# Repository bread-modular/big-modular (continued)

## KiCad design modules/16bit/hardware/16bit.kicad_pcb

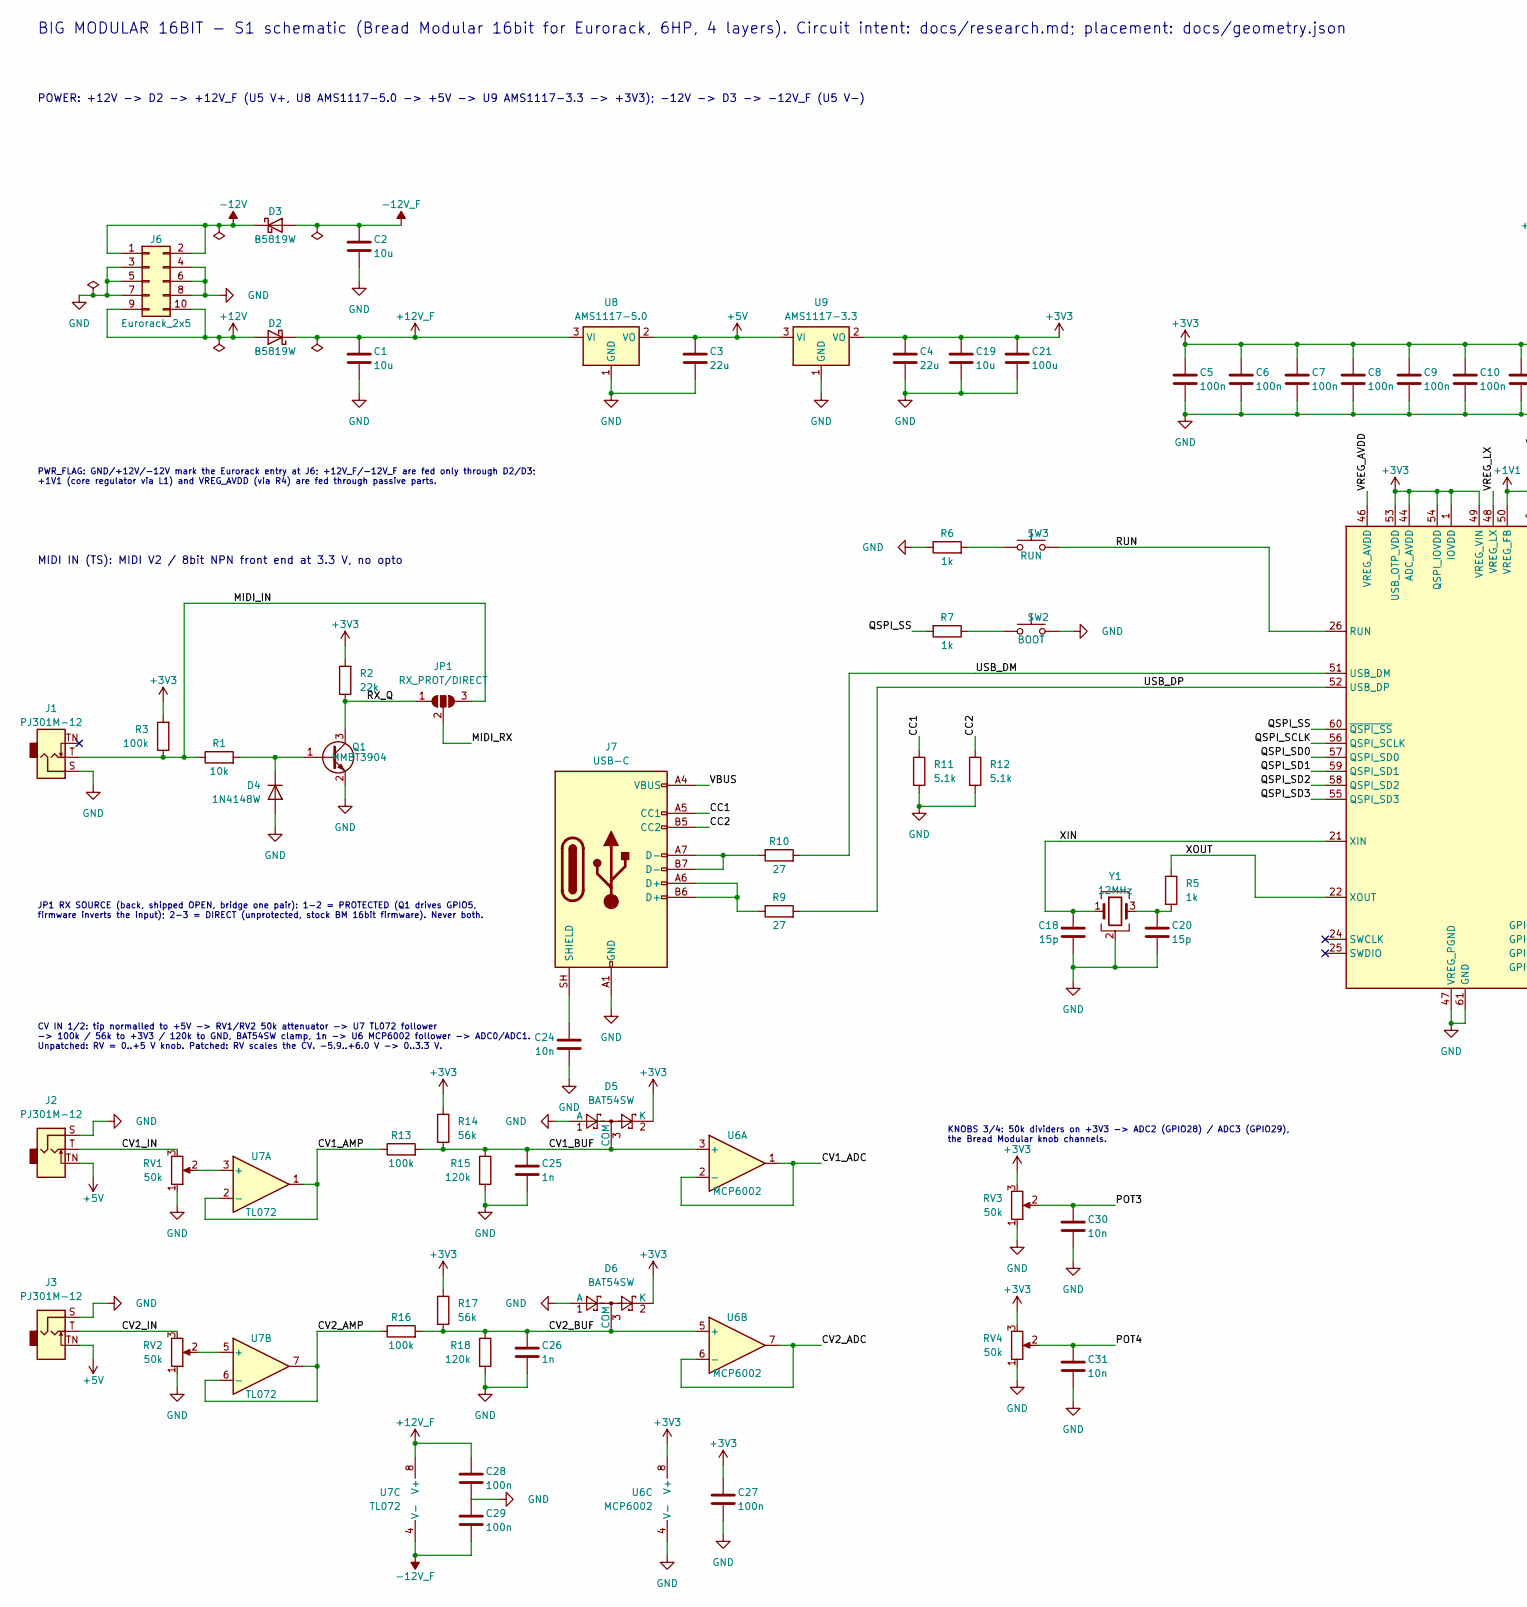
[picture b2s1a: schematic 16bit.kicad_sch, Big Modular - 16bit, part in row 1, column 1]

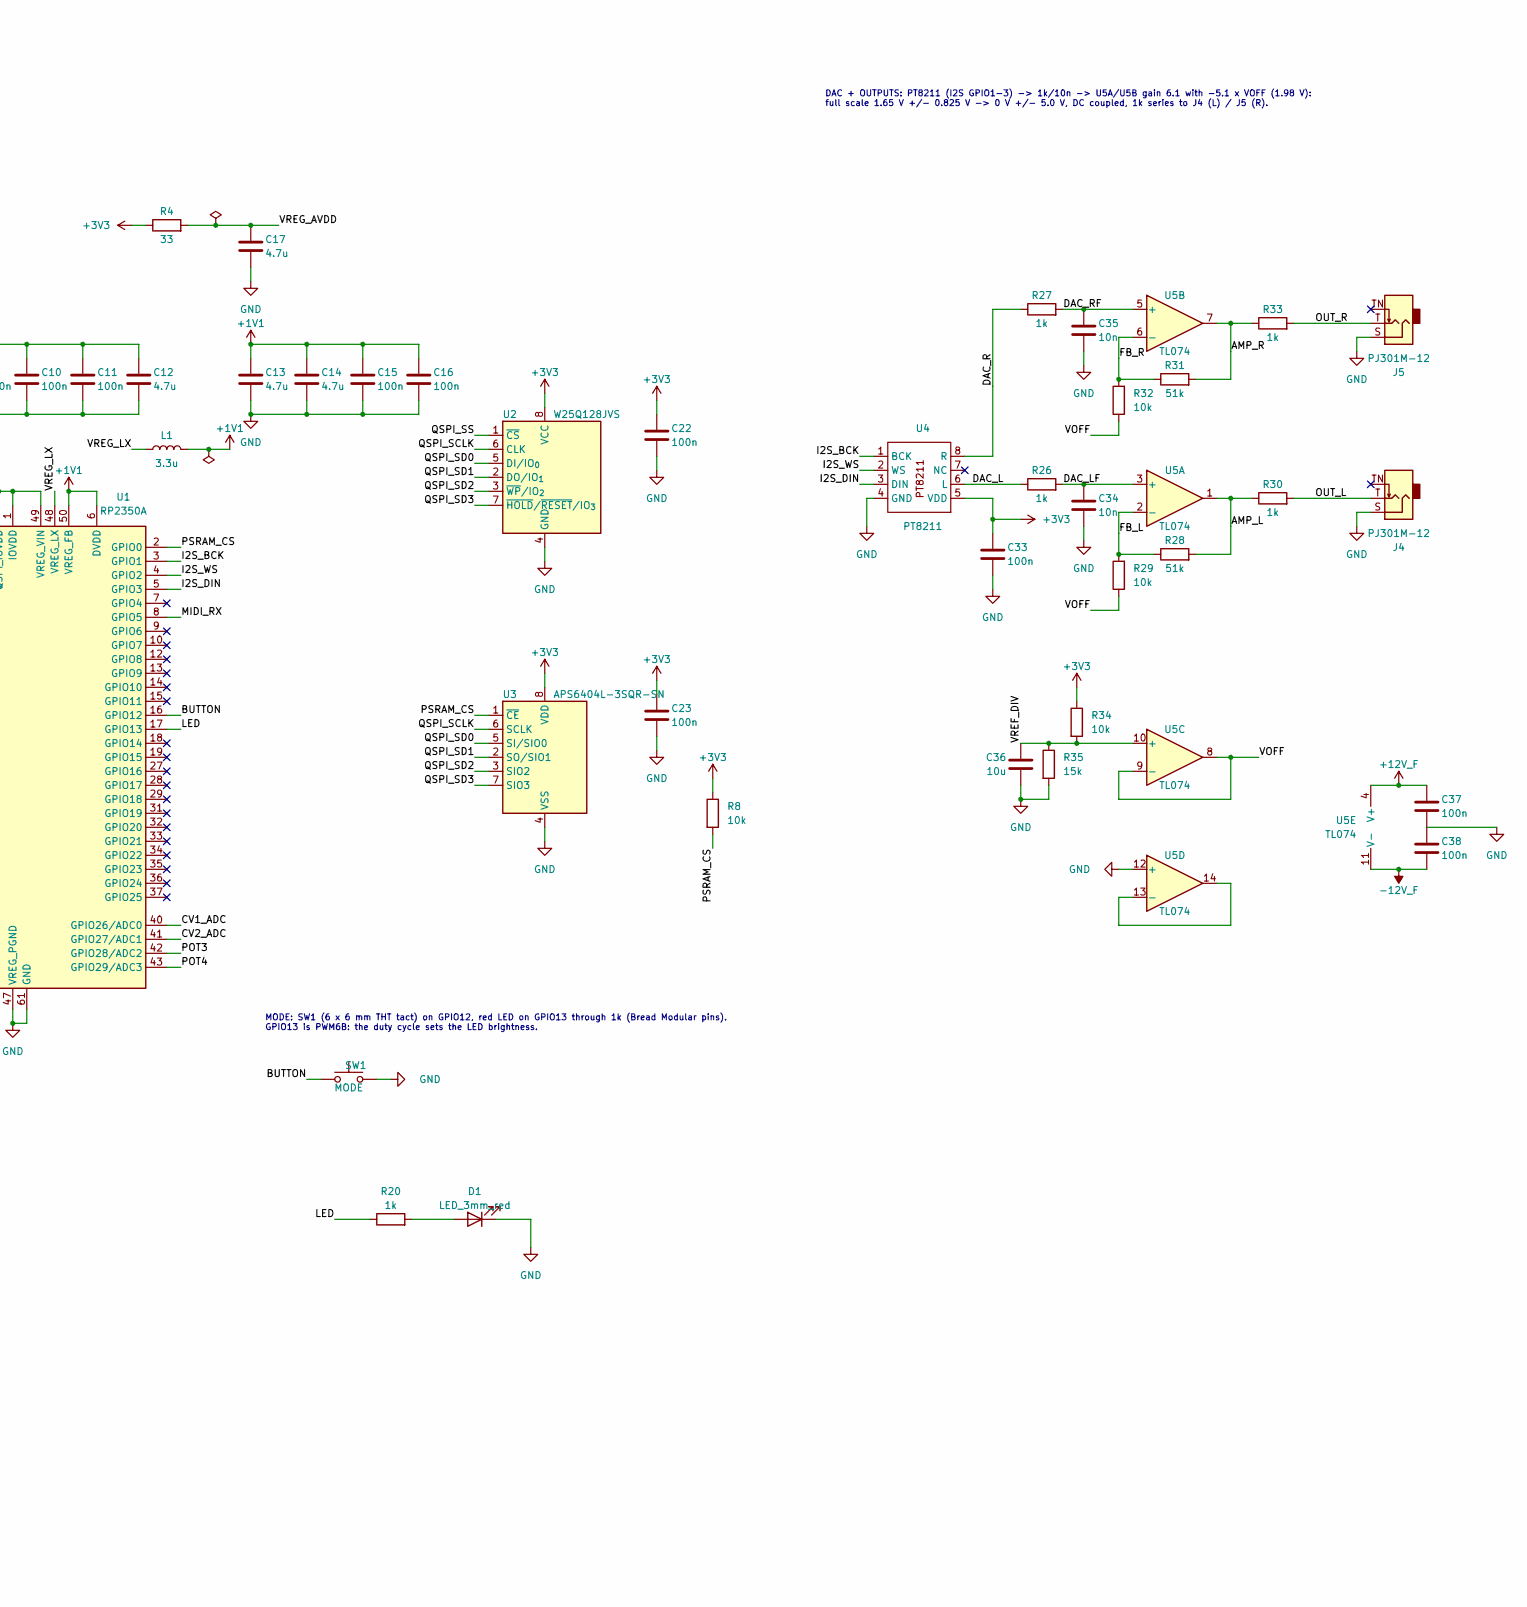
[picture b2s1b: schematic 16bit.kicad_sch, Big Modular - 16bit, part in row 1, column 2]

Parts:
C1, C2, C19, C36: 10u; C_0805_2012Metric; Voltage 25V; MPN CL21A106KAYNNNE; LCSC C15850
C3, C4: 22u; C_0805_2012Metric; Voltage 25V; MPN CL21A226MAQNNNE; LCSC C45783
C5, C6, C7, C8, C9, C10, C11, C22, C23, C33: 100n; C_0402_1005Metric; Voltage 16V; MPN CL05B104KO5NNNC; LCSC C1525
C12, C13: 4.7u; C_0402_1005Metric_small_pads; Voltage 10V; MPN CL05A475MP5NRNC; LCSC C23733
C14, C17: 4.7u; C_0402_1005Metric; Voltage 10V; MPN CL05A475MP5NRNC; LCSC C23733
C15, C16: 100n; C_0402_1005Metric; Voltage 10V; MPN CL05B104KO5NNNC; LCSC C1525
C18, C20: 15p; C_0402_1005Metric; Voltage 50V; MPN 0402CG150J500NT; LCSC C1548
C21: 100u; C_1206_3216Metric; Voltage 6.3V; MPN CL31A107MQHNNNE; LCSC C15008
C24: 10n; C_0402_1005Metric; Voltage 50V; MPN CL05B103KB5NNNC; LCSC C15195
C25, C26: 1n; C_0603_1608Metric; Voltage 50V; MPN CL10B102KB8NNNC; LCSC C1588
C27, C28, C29, C37, C38: 100n; C_0603_1608Metric; Voltage 50V; MPN CC0603KRX7R9BB104; LCSC C14663
C30, C31, C34, C35: 10n; C_0603_1608Metric; Voltage 50V; MPN 0603B103K500NT; LCSC C57112
D1: LED_3mm_red; LED_D3.0mm
D2, D3: B5819W; D_SOD-123; MPN B5819W SL; LCSC C8598
D4: 1N4148W; D_SOD-123; MPN 1N4148W; LCSC C81598
D5, D6: BAT54SW; SOT-323_SC-70; MPN BAT54SWT1G; LCSC C78260
J1, J2, J3, J4, J5: PJ301M-12; Jack_3.5mm_QingPu_WQP-PJ301M-12_Vertical
J6: Eurorack_2x5; PinHeader_2x05_P2.54mm_Vertical
J7: USB-C; USB_C_Receptacle_HRO_TYPE-C-31-M-12; MPN TYPE-C-31-M-12; LCSC C165948
JP1: RX_PROT/DIRECT; SolderJumper-3_P1.3mm_Open_RoundedPad1.0x1.5mm
L1: 3.3u; L_pol_2016; MPN FTC201610S3R3MBCA; LCSC C5832345
Q1: MMBT3904; SOT-23; MPN MMBT3904(RANGE:100-300); LCSC C20526
R1, R29, R32, R34: 10k; R_0603_1608Metric; MPN 0603WAF1002T5E; LCSC C25804
R2: 22k; R_0603_1608Metric; MPN 0603WAF2202T5E; LCSC C31850
R3, R13, R16: 100k; R_0603_1608Metric; MPN 0603WAF1003T5E; LCSC C25803
R4: 33; R_0402_1005Metric; MPN 0402WGF330JTCE; LCSC C25105
R5, R6, R7: 1k; R_0402_1005Metric; MPN 0402WGF1001TCE; LCSC C11702
R8: 10k; R_0402_1005Metric; MPN 0402WGF1002TCE; LCSC C25744
R9, R10: 27; R_0402_1005Metric; MPN 0402WGF270JTCE; LCSC C25100
R11, R12: 5.1k; R_0402_1005Metric; MPN 0402WGF5101TCE; LCSC C25905
R14, R17: 56k; R_0603_1608Metric; MPN 0603WAF5602T5E; LCSC C23206
R15, R18: 120k; R_0603_1608Metric; MPN 0603WAF1203T5E; LCSC C25808
R20, R26, R27: 1k; R_0603_1608Metric; MPN 0603WAF1001T5E; LCSC C21190
R28, R31: 51k; R_0603_1608Metric; MPN 0603WAF5102T5E; LCSC C23196
R30, R33: 1k; R_1206_3216Metric; MPN 1206W4F1001T5E; LCSC C4410
R35: 15k; R_0603_1608Metric; MPN 0603WAF1502T5E; LCSC C22809
RV1, RV2, RV3, RV4: 50k; Potentiometer_RV09
SW1: MODE; SW_PUSH_6mm_H7.3mm; MPN 6x6x7 mm THT tact switch, 4 pins (gener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
SW2: BOOT; K2-1808SN-A4SW-01; MPN K2-1808SN-A4SW-01; LCSC C92589
SW3: RUN; K2-1808SN-A4SW-01; MPN K2-1808SN-A4SW-01; LCSC C92589
U1: RP2350A; RP2350-QFN-60-1EP_7x7_P0.4mm_EP3.4x3.4mm_ThermalVias; MPN RP2350A; LCSC C42411118
U2: W25Q128JVS; SOIC-8_5.3x5.3mm_P1.27mm; MPN W25Q128JVSIQ; LCSC C97521
U3: APS6404L-3SQR-SN; SOIC-8 Generic; MPN 4677; LCSC C17430771
U4: PT8211; SOIC-8_3.9x4.9mm_P1.27mm; MPN TM8211-TA2302; LCSC C22381766
U5: TL074; SOIC-14_3.9x8.7mm_P1.27mm; MPN TL074CDR; LCSC C12594
U6: MCP6002; SOIC-8_3.9x4.9mm_P1.27mm; MPN MCP6002T-I/SN; LCSC C7377
U7: TL072; SOIC-8_3.9x4.9mm_P1.27mm; MPN TL072CDT; LCSC C6961
U8: AMS1117-5.0; SOT-223-3_TabPin2; MPN AMS1117-5.0; LCSC C6187
U9: AMS1117-3.3; SOT-223-3_TabPin2; MPN AMS1117-3.3; LCSC C6186
Y1: 12MHz; Crystal_SMD_3225-4Pin_3.2x2.5mm; MPN ABM8-272-T3; LCSC C20625731

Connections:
+1V1: C13.1, C14.1, C15.1, C16.1, L1.2, U1.6 (DVDD), U1.23 (DVDD), U1.39 (DVDD), U1.50 (VREG_FB)
+3V3: C4.1, C5.1, C6.1, C7.1, C8.1, C9.1, C10.1, C11.1, C12.1, C19.1, C21.1, C22.1, C23.1, C27.1, C33.1, D5.2 (K), D6.2 (K), R2.2, R3.2, R4.1, R8.1, R14.1, R17.1, R34.1, RV3.3, RV4.3, U1.1 (IOVDD), U1.11 (IOVDD), U1.20 (IOVDD), U1.30 (IOVDD), U1.38 (IOVDD), U1.44 (ADC_AVDD), U1.45 (IOVDD), U1.49 (VREG_VIN), U1.53 (USB_OTP_VDD), U1.54 (QSPI_IOVDD), U2.8 (VCC), U3.8 (VDD), U4.5 (VDD), U6.8 (V+), U9.2 (VO)
+5V: C3.1, J2.TN, J3.TN, U8.2 (VO), U9.3 (VI)
+12V: D2.2 (A), J6.9, J6.10
+12V_F: C1.1, C28.1, C37.1, D2.1 (K), U5.4 (V+), U7.8 (V+), U8.3 (VI)
-12V: D3.1 (K), J6.1, J6.2
-12V_F: C2.2, C29.2, C38.2, D3.2 (A), U5.11 (V-), U7.4 (V-)
/AMP_L: R28.2, R30.1, U5.1
/AMP_R: R31.2, R33.1, U5.7
/BUTTON: SW1.1, U1.16 (GPIO12)
/CC1: J7.A5 (CC1), R11.1
/CC2: J7.B5 (CC2), R12.1
/CV1_ADC: U1.40 (GPIO26/ADC0), U6.1, U6.2 (-)
/CV1_AMP: R13.1, U7.1, U7.2 (-)
/CV1_BUF: C25.1, D5.3 (COM), R13.2, R14.2, R15.1, U6.3 (+)
/CV1_IN: J2.T, RV1.3
/CV2_ADC: U1.41 (GPIO27/ADC1), U6.6 (-), U6.7
/CV2_AMP: R16.1, U7.6 (-), U7.7
/CV2_BUF: C26.1, D6.3 (COM), R16.2, R17.2, R18.1, U6.5 (+)
/CV2_IN: J3.T, RV2.3
/DAC_L: R26.1, U4.6 (L)
/DAC_LF: C34.1, R26.2, U5.3 (+)
/DAC_R: R27.1, U4.8 (R)
/DAC_RF: C35.1, R27.2, U5.5 (+)
/FB_L: R28.1, R29.2, U5.2 (-)
/FB_R: R31.1, R32.2, U5.6 (-)
/I2S_BCK: U1.3 (GPIO1), U4.1 (BCK)
/I2S_DIN: U1.5 (GPIO3), U4.3 (DIN)
/I2S_WS: U1.4 (GPIO2), U4.2 (WS)
/LED: R20.1, U1.17 (GPIO13)
/MIDI_IN: J1.T, JP1.3 (B), R1.1, R3.1
/MIDI_RX: JP1.2 (C), U1.8 (GPIO5)
/OUT_L: J4.T, R30.2
/OUT_R: J5.T, R33.2
/POT3: C30.1, RV3.2, U1.42 (GPIO28/ADC2)
/POT4: C31.1, RV4.2, U1.43 (GPIO29/ADC3)
/PSRAM_CS: R8.2, U1.2 (GPIO0), U3.1 (~CE)
/QSPI_SCLK: U1.56 (QSPI_SCLK), U2.6 (CLK), U3.6 (SCLK)
/QSPI_SD0: U1.57 (QSPI_SD0), U2.5 (DI/IO_{0}), U3.5 (SI/SIO0)
/QSPI_SD1: U1.59 (QSPI_SD1), U2.2 (DO/IO_{1}), U3.2 (SO/SIO1)
/QSPI_SD2: U1.58 (QSPI_SD2), U2.3 (~WP/IO_{2}), U3.3 (SIO2)
/QSPI_SD3: U1.55 (QSPI_SD3), U2.7 (~HOLD/~RESET/IO_{3}), U3.7 (SIO3)
/QSPI_SS: R7.2, U1.60 (~QSPI_SS), U2.1 (~CS)
/RUN: SW3.2, U1.26 (RUN)
/RX_Q: JP1.1 (A), Q1.3 (C), R2.1
/USB_DM: R10.2, U1.51 (USB_DM)
/USB_DP: R9.2, U1.52 (USB_DP)
/VBUS: J7.A4 (VBUS), J7.A9 (VBUS), J7.B4 (VBUS), J7.B9 (VBUS)
/VOFF: R29.1, R32.1, U5.8, U5.9 (-)
/VREF_DIV: C36.1, R34.2, R35.1, U5.10 (+)
/VREG_AVDD: C17.1, R4.2, U1.46 (VREG_AVDD)
/VREG_LX: L1.1, U1.48 (VREG_LX)
/XIN: C18.1, U1.21 (XIN), Y1.1
/XOUT: R5.1, U1.22 (XOUT)
GND: C1.2, C2.1, C3.2, C4.2, C5.2, C6.2, C7.2, C8.2, C9.2, C10.2, C11.2, C12.2, C13.2, C14.2, C15.2, C16.2, C17.2, C18.2, C19.2, C20.2, C21.2, C22.2, C23.2, C24.2, C25.2, C26.2, C27.2, C28.2, C29.1, C30.2, C31.2, C33.2, C34.2, C35.2, C36.2, C37.2, C38.1, D1.1 (K), D4.2 (A), D5.1 (A), D6.1 (A), J1.S, J2.S, J3.S, J4.S, J5.S, J6.3, J6.4, J6.5, J6.6, J6.7, J6.8, J7.A1 (GND), J7.A12 (GND), J7.B1 (GND), J7.B12 (GND), Q1.2 (E), R6.1, R11.2, R12.2, R15.2, R18.2, R35.2, RV1.1, RV2.1, RV3.1, RV4.1, SW1.2, SW2.2, U1.47 (VREG_PGND), U1.61 (GND), U2.4 (GND), U3.4 (VSS), U4.4 (GND), U5.12 (+), U6.4 (V-), U8.1 (GND), U9.1 (GND), Y1.2 (G), Y1.4 (G)
unnamed: C20.1, R5.2, Y1.3
unnamed: D1.2 (A), R20.2
unnamed: D4.1 (K), Q1.1 (B), R1.2
unnamed: J7.A6 (D+), J7.B6 (D+), R9.1
unnamed: J7.A7 (D-), J7.B7 (D-), R10.1
unnamed: C24.1, J7.SH (SHIELD)
unnamed: R6.2, SW3.1
unnamed: R7.1, SW2.1
unnamed: U5.13 (-), U5.14
unnamed: RV1.2, U7.3 (+)
unnamed: RV2.2, U7.5 (+)

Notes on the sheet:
BIG MODULAR 16BIT - S1 schematic (Bread Modular 16bit for Eurorack, 6HP, 4 layers). Circuit intent: docs/research.md; placement: docs/geometry.json
DAC + OUTPUTS: PT8211 (I2S GPIO1-3) -> 1k/10n -> U5A/U5B gain 6.1 with -5.1 x VOFF (1.98 V): full scale 1.65 V +/- 0.825 V -> 0 V +/- 5.0 V, DC coupled, 1k series to J4 (L) / J5 (R).
MIDI IN (TS): MIDI V2 / 8bit NPN front end at 3.3 V, no opto
POWER: +12V -> D2 -> +12V_F (U5 V+, U8 AMS1117-5.0 -> +5V -> U9 AMS1117-3.3 -> +3V3); -12V -> D3 -> -12V_F (U5 V-)
PWR_FLAG: GND/+12V/-12V mark the Eurorack entry at J6; +12V_F/-12V_F are fed only through D2/D3; +1V1 (core regulator via L1) and VREG_AVDD (via R4) are fed through passive parts.
MODE: SW1 (6 x 6 mm THT tact) on GPIO12, red LED on GPIO13 through 1k (Bread Modular pins). GPIO13 is PWM6B: the duty cycle sets the LED brightness.
CV IN 1/2: tip normalled to +5V -> RV1/RV2 50k attenuator -> U7 TL072 follower -> 100k / 56k to +3V3 / 120k to GND, BAT54SW clamp, 1n -> U6 MCP6002 follower -> ADC0/ADC1. Unpatched: RV = 0..+5 V knob. Patched: RV scales the CV. -5.9..+6.0 V -> 0..3.3 V.
KNOBS 3/4: 50k dividers on +3V3 -> ADC2 (GPIO28) / ADC3 (GPIO29), the Bread Modular knob channels.
JP1 RX SOURCE (back, shipped OPEN, bridge one pair): 1-2 = PROTECTED (Q1 drives GPIO5, firmware inverts the input); 2-3 = DIRECT (unprotected, stock BM 16bit firmware). Never both.

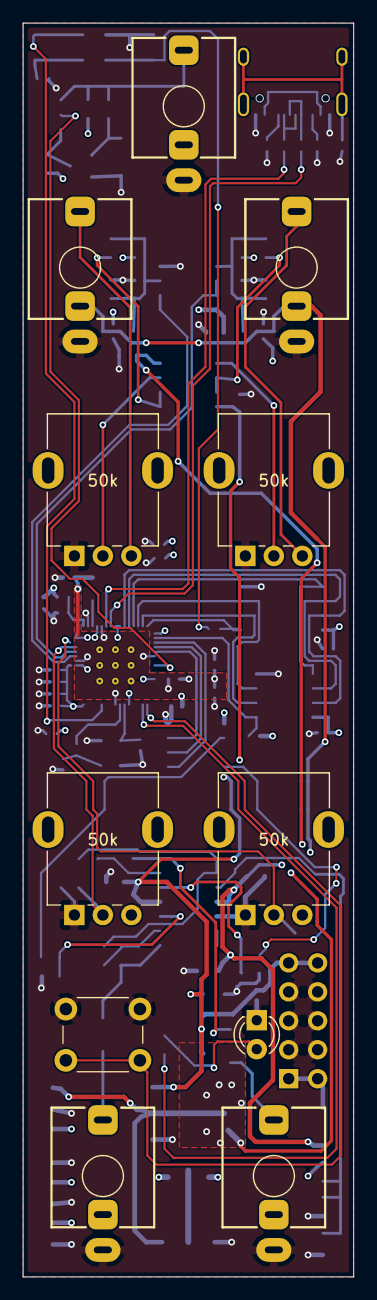
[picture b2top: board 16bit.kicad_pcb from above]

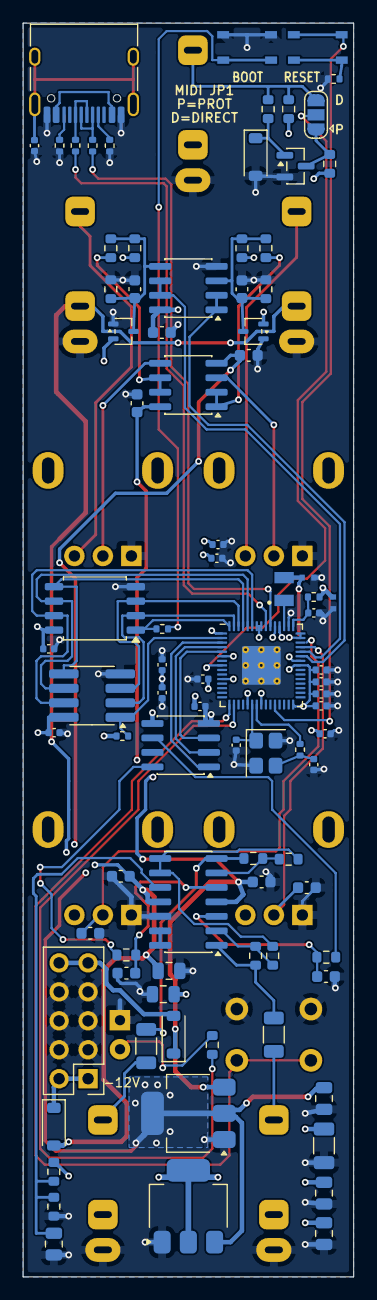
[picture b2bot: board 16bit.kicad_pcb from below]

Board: 4 copper layers, 29.0 x 110.0 mm, 99 parts (88 on the bottom side), 66 nets.

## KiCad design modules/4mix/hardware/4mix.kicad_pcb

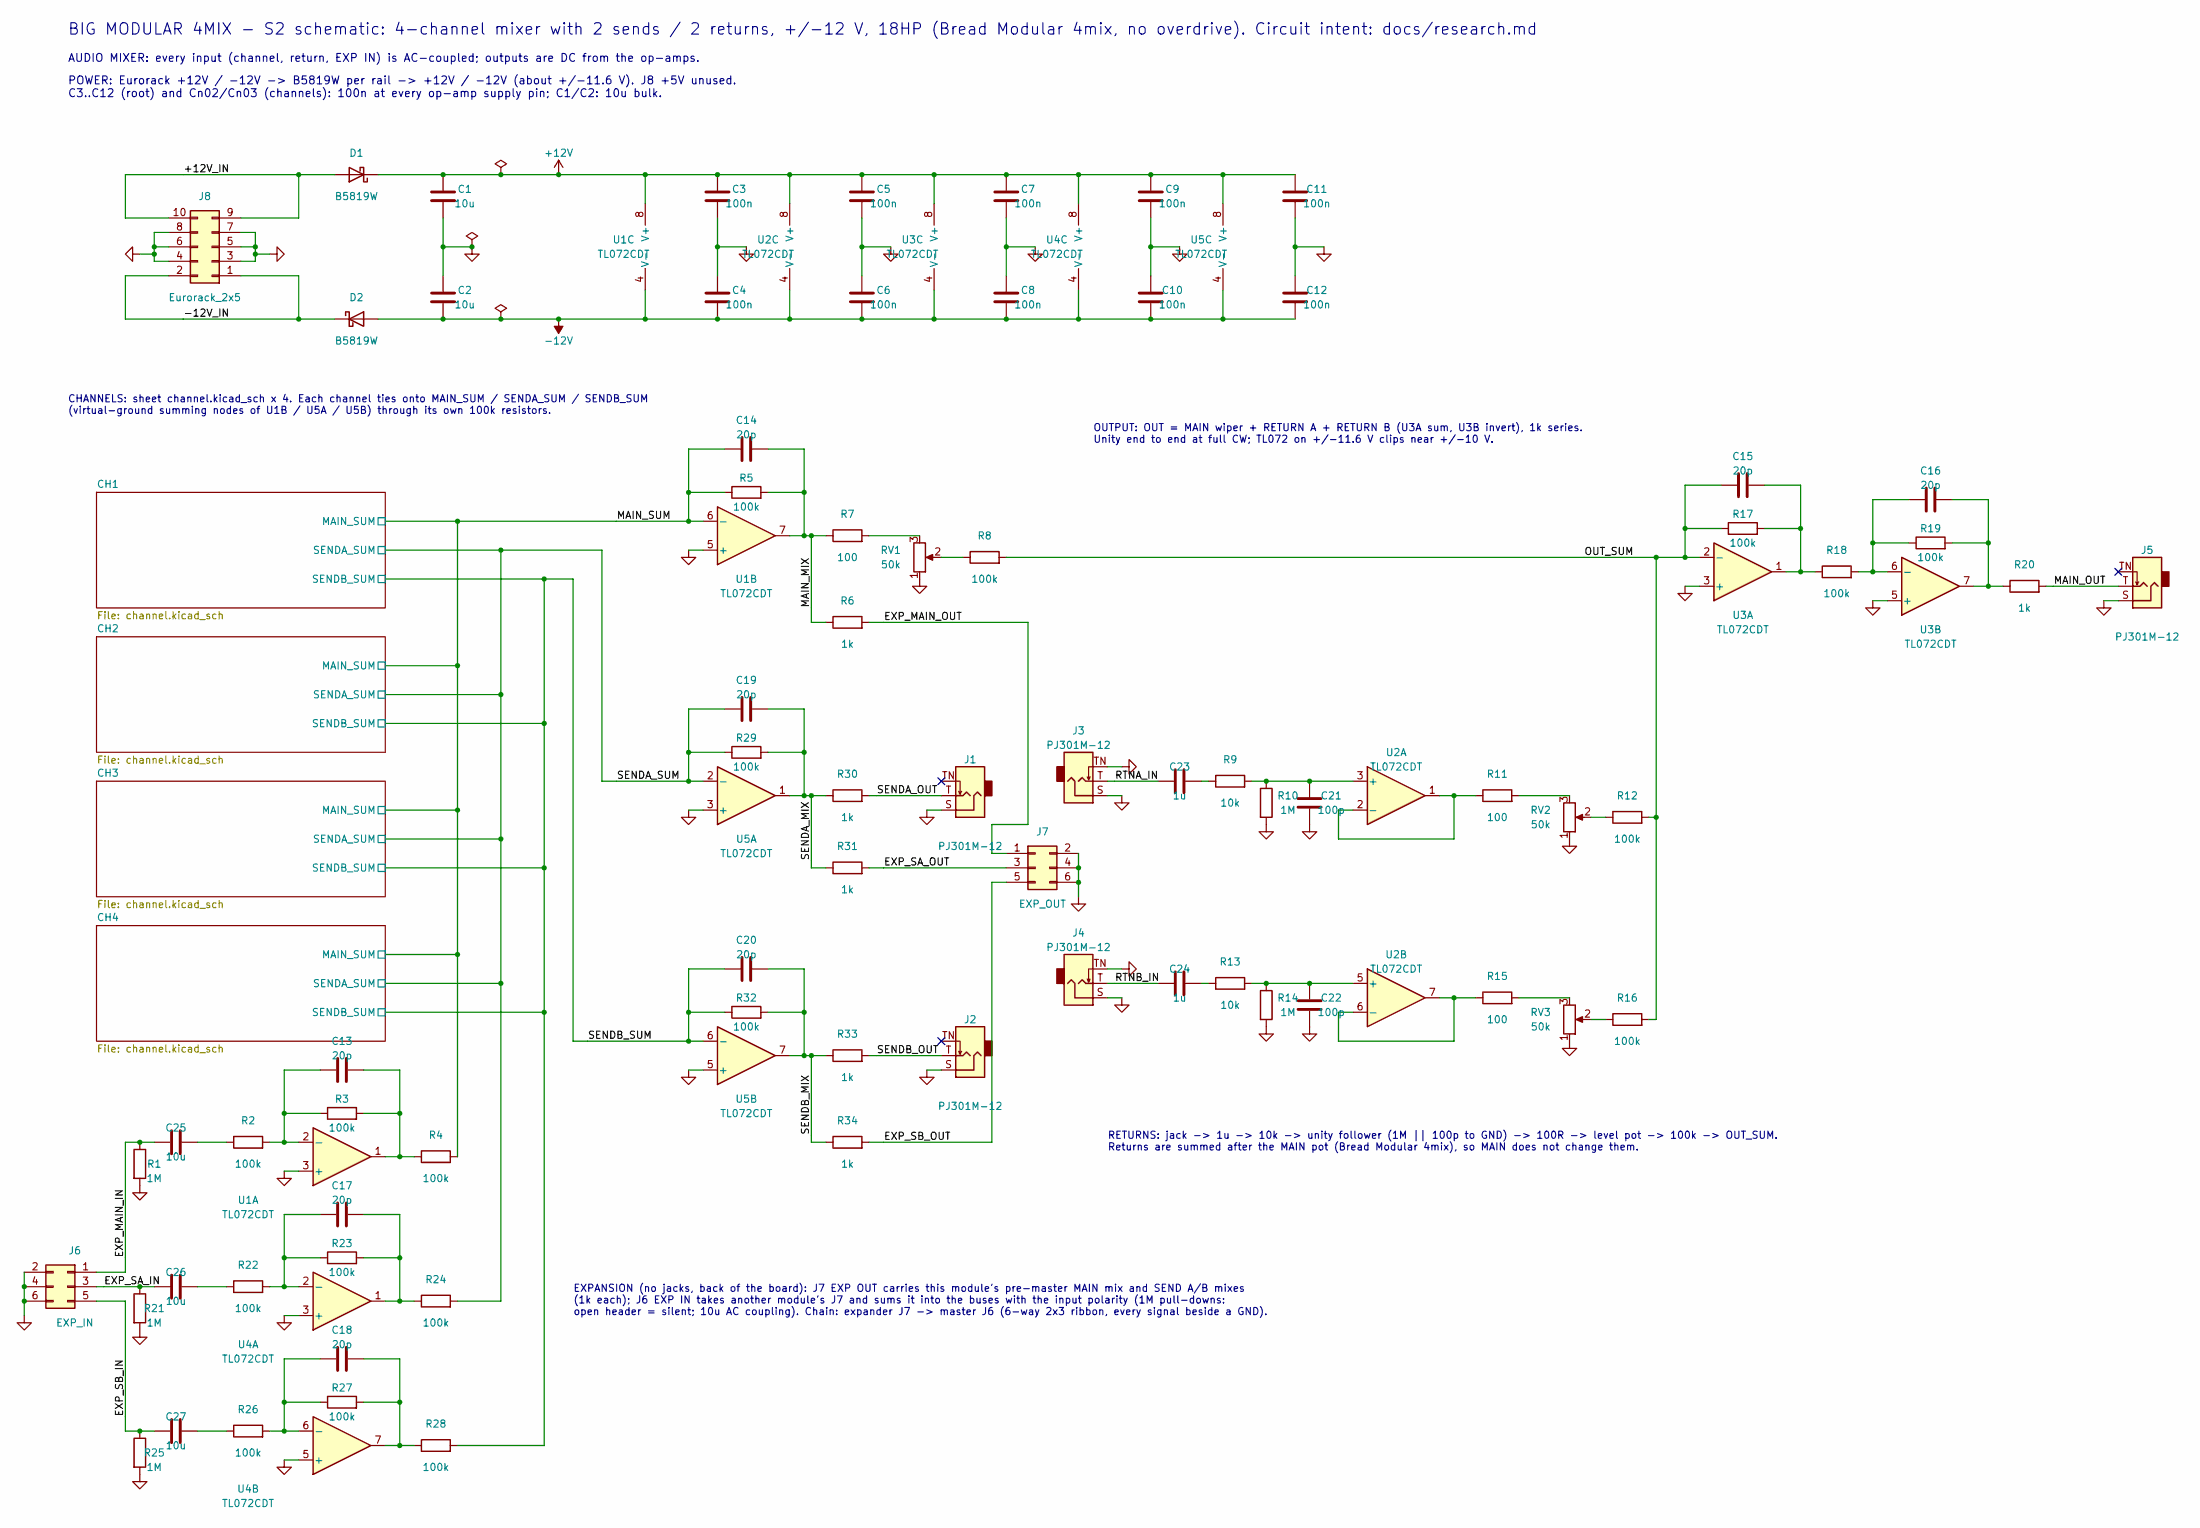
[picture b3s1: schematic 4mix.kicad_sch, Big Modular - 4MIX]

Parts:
C1, C2, C25, C26, C27: 10u; C_0805_2012Metric; Voltage 25V; MPN CL21A106KAYNNNE; LCSC C15850
C3, C4, C5, C6, C7, C8, C9, C10, C11, C12: 100n; C_0603_1608Metric; Voltage 50V; MPN CC0603KRX7R9BB104; LCSC C14663
C13, C14, C15, C16, C17, C18, C19, C20: 20p; C_0603_1608Metric; Voltage 50V; MPN CL10C200JB8NNNC; LCSC C1648
C21, C22: 100p; C_0603_1608Metric; Voltage 50V; MPN CL10C101JB8NNNC; LCSC C14858
C23, C24: 1u; C_0603_1608Metric; Voltage 25V; MPN CL10A105KB8NNNC; LCSC C15849
D1, D2: B5819W; D_SOD-123; MPN B5819W SL; LCSC C8598
J1, J2, J3, J4, J5: PJ301M-12; Jack_3.5mm_QingPu_WQP-PJ301M-12_Vertical
J6: EXP_IN; PinHeader_2x03_P2.54mm_Vertical
J7: EXP_OUT; PinHeader_2x03_P2.54mm_Vertical
J8: Eurorack_2x5; PinHeader_2x05_P2.54mm_Vertical
R1, R10, R14, R21, R25: 1M; R_0603_1608Metric; MPN 0603WAF1004T5E; LCSC C22935
R2, R3, R4, R5, R8, R12, R16, R17, R18, R19, R22, R23, R24, R26, R27, R28, R29, R32: 100k; R_0603_1608Metric; MPN 0603WAF1003T5E; LCSC C25803
R6, R31, R34: 1k; R_0603_1608Metric; MPN 0603WAF1001T5E; LCSC C21190
R7, R11, R15: 100; R_0603_1608Metric; MPN 0603WAF1000T5E; LCSC C22775
R9, R13: 10k; R_0603_1608Metric; MPN 0603WAF1002T5E; LCSC C25804
R20, R30, R33: 1k; R_2512_6332Metric; MPN 25121WF1001T4E; LCSC C54315
RV1, RV2, RV3: 50k; Potentiometer_RV09
U1, U2, U3, U4, U5: TL072CDT; SOIC-8_3.9x4.9mm_P1.27mm; MPN TL072CDT; LCSC C6961

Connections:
+12V: C1.1, C3.1, C5.1, C7.1, C9.1, C11.1, D1.1 (K), U1.8 (V+), U2.8 (V+), U3.8 (V+), U4.8 (V+), U5.8 (V+); also elsewhere on the board
-12V: C2.2, C4.2, C6.2, C8.2, C10.2, C12.2, D2.2 (A), U1.4 (V-), U2.4 (V-), U3.4 (V-), U4.4 (V-), U5.4 (V-); also elsewhere on the board
/+12V_IN: D1.2 (A), J8.9, J8.10
/-12V_IN: D2.1 (K), J8.1, J8.2
/EXP_MAIN_IN: C25.1, J6.1, R1.1
/EXP_MAIN_OUT: J7.1, R6.2
/EXP_SA_IN: C26.1, J6.3, R21.1
/EXP_SA_OUT: J7.3, R31.2
/EXP_SB_IN: C27.1, J6.5, R25.1
/EXP_SB_OUT: J7.5, R34.2
/MAIN_MIX: C14.2, R5.2, R6.1, R7.1, U1.7
/MAIN_OUT: J5.T, R20.2
/MAIN_SUM: C14.1, R4.2, R5.1, U1.6 (-); also elsewhere on the board
/OUT_SUM: C15.1, R8.2, R12.2, R16.2, R17.1, U3.2 (-)
/RTNA_IN: C23.1, J3.T
/RTNB_IN: C24.1, J4.T
/SENDA_MIX: C19.2, R29.2, R30.1, R31.1, U5.1
/SENDA_OUT: J1.T, R30.2
/SENDA_SUM: C19.1, R24.2, R29.1, U5.2 (-); also elsewhere on the board
/SENDB_MIX: C20.2, R32.2, R33.1, R34.1, U5.7
/SENDB_OUT: J2.T, R33.2
/SENDB_SUM: C20.1, R28.2, R32.1, U5.6 (-); also elsewhere on the board
GND: C1.2, C2.1, C3.2, C4.1, C5.2, C6.1, C7.2, C8.1, C9.2, C10.1, C11.2, C12.1, C21.2, C22.2, J1.S, J2.S, J3.S, J3.TN, J4.S, J4.TN, J5.S, J6.2, J6.4, J6.6, J7.2, J7.4, J7.6, J8.3, J8.4, J8.5, J8.6, J8.7, J8.8, R1.2, R10.2, R14.2, R21.2, R25.2, RV1.1, RV2.1, RV3.1, U1.3 (+), U1.5 (+), U3.3 (+), U3.5 (+), U4.3 (+), U4.5 (+), U5.3 (+), U5.5 (+); also elsewhere on the board
unnamed: C13.2, R3.2, R4.1, U1.1
unnamed: C15.2, R17.2, R18.1, U3.1
unnamed: C16.2, R19.2, R20.1, U3.7
unnamed: C17.2, R23.2, R24.1, U4.1
unnamed: C18.2, R27.2, R28.1, U4.7
unnamed: C23.2, R9.1
unnamed: C24.2, R13.1
unnamed: C25.2, R2.1
unnamed: C26.2, R22.1
unnamed: C27.2, R26.1
unnamed: R7.2, RV1.3
unnamed: R8.1, RV1.2
unnamed: R11.2, RV2.3
unnamed: R12.1, RV2.2
unnamed: R15.2, RV3.3
unnamed: R16.1, RV3.2
unnamed: C13.1, R2.2, R3.1, U1.2 (-)
unnamed: C21.1, R9.2, R10.1, U2.3 (+)
unnamed: R11.1, U2.1, U2.2 (-)
unnamed: C22.1, R13.2, R14.1, U2.5 (+)
unnamed: R15.1, U2.6 (-), U2.7
unnamed: C16.1, R18.2, R19.1, U3.6 (-)
unnamed: C17.1, R22.2, R23.1, U4.2 (-)
unnamed: C18.1, R26.2, R27.1, U4.6 (-)

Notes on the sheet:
BIG MODULAR 4MIX - S2 schematic: 4-channel mixer with 2 sends / 2 returns, +/-12 V, 18HP (Bread Modular 4mix, no overdrive). Circuit intent: docs/research.md
AUDIO MIXER: every input (channel, return, EXP IN) is AC-coupled; outputs are DC from the op-amps.
CHANNELS: sheet channel.kicad_sch x 4. Each channel ties onto MAIN_SUM / SENDA_SUM / SENDB_SUM (virtual-ground summing nodes of U1B / U5A / U5B) through its own 100k resistors.
OUTPUT: OUT = MAIN wiper + RETURN A + RETURN B (U3A sum, U3B invert), 1k series. Unity end to end at full CW; TL072 on +/-11.6 V clips near +/-10 V.
POWER: Eurorack +12V / -12V -> B5819W per rail -> +12V / -12V (about +/-11.6 V). J8 +5V unused. C3..C12 (root) and Cn02/Cn03 (channels): 100n at every op-amp supply pin; C1/C2: 10u bulk.
EXPANSION (no jacks, back of the board): J7 EXP OUT carries this module's pre-master MAIN mix and SEND A/B mixes (1k each); J6 EXP IN takes another module's J7 and sums it into the buses with the input polarity (1M pull-downs: open header = silent; 10u AC coupling). Chain: expander J7 -> master J6 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
RETURNS: jack -> 1u -> 10k -> unity follower (1M || 100p to GND) -> 100R -> level pot -> 100k -> OUT_SUM. Returns are summed after the MAIN pot (Bread Modular 4mix), so MAIN does not change them.

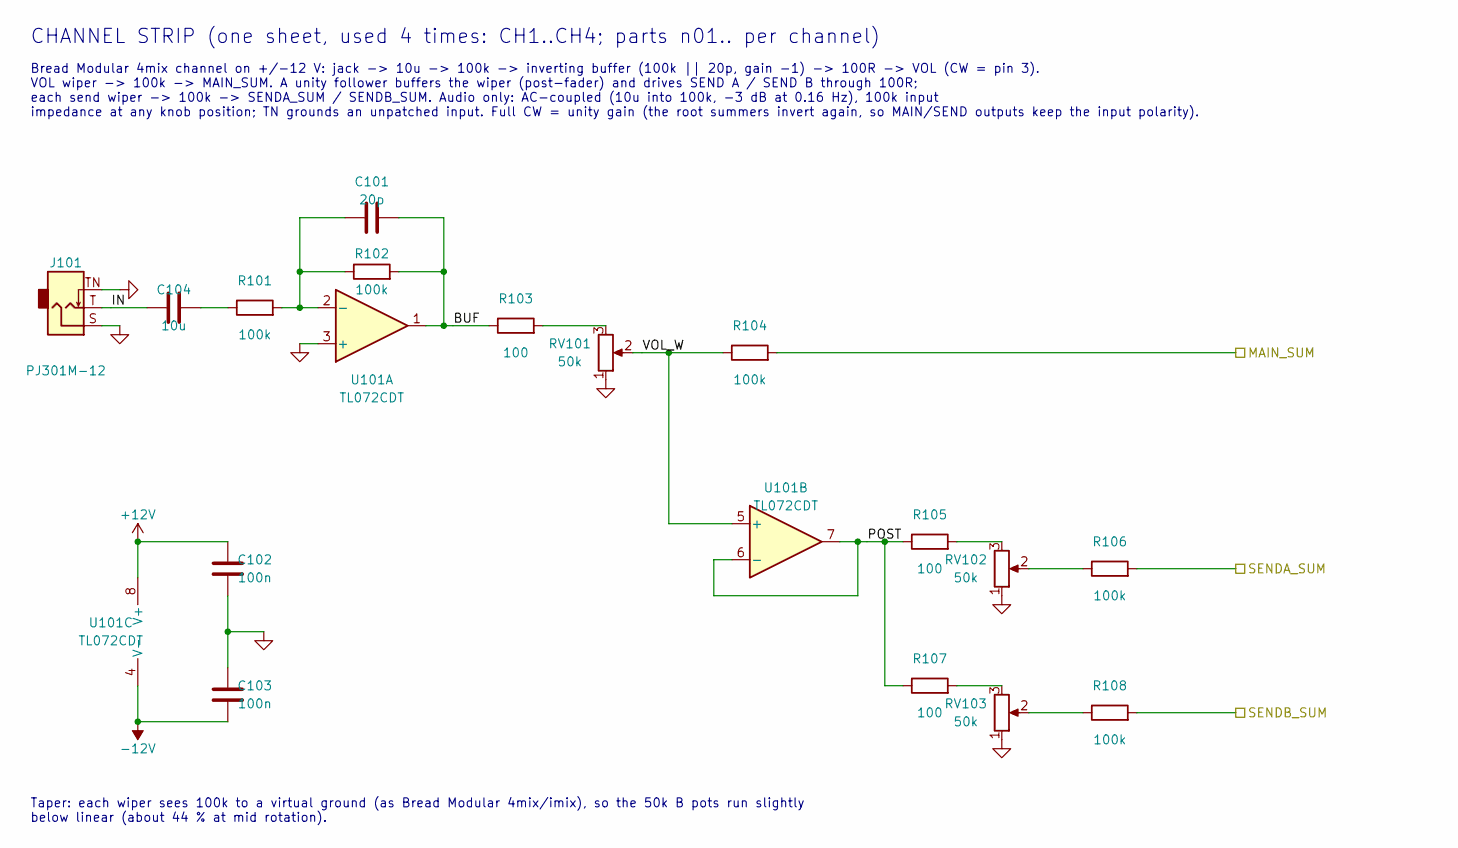
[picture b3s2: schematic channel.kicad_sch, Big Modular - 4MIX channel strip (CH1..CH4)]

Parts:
C101: 20p; C_0603_1608Metric; Voltage 50V; MPN CL10C200JB8NNNC; LCSC C1648
C102, C103: 100n; C_0603_1608Metric; Voltage 50V; MPN CC0603KRX7R9BB104; LCSC C14663
C104: 10u; C_0805_2012Metric; Voltage 25V; MPN CL21A106KAYNNNE; LCSC C15850
J101: PJ301M-12; Jack_3.5mm_QingPu_WQP-PJ301M-12_Vertical
R101, R102, R104, R106, R108: 100k; R_0603_1608Metric; MPN 0603WAF1003T5E; LCSC C25803
R103, R105, R107: 100; R_0603_1608Metric; MPN 0603WAF1000T5E; LCSC C22775
RV101, RV102, RV103: 50k; Potentiometer_RV09
U101: TL072CDT; SOIC-8_3.9x4.9mm_P1.27mm; MPN TL072CDT; LCSC C6961

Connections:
+12V: C102.1, U101.8 (V+); also elsewhere on the board
-12V: C103.2, U101.4 (V-); also elsewhere on the board
/CH1/BUF: C101.2, R102.2, R103.1, U101.1
/CH1/IN: C104.1, J101.T
/CH1/POST: R105.1, R107.1, U101.6 (-), U101.7
/CH1/VOL_W: R104.1, RV101.2, U101.5 (+)
/MAIN_SUM: R104.2; also elsewhere on the board
/SENDA_SUM: R106.2; also elsewhere on the board
/SENDB_SUM: R108.2; also elsewhere on the board
GND: C102.2, C103.1, J101.S, J101.TN, RV101.1, RV102.1, RV103.1, U101.3 (+); also elsewhere on the board
unnamed: C104.2, R101.1
unnamed: R103.2, RV101.3
unnamed: R105.2, RV102.3
unnamed: R106.1, RV102.2
unnamed: R107.2, RV103.3
unnamed: R108.1, RV103.2
unnamed: C101.1, R101.2, R102.1, U101.2 (-)

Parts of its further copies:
C201, C301, C401: 20p; C_0603_1608Metric; Voltage 50V; MPN CL10C200JB8NNNC; LCSC C1648
C202, C203, C302, C303, C402, C403: 100n; C_0603_1608Metric; Voltage 50V; MPN CC0603KRX7R9BB104; LCSC C14663
C204, C304, C404: 10u; C_0805_2012Metric; Voltage 25V; MPN CL21A106KAYNNNE; LCSC C15850
J201, J301, J401: PJ301M-12; Jack_3.5mm_QingPu_WQP-PJ301M-12_Vertical
R201, R202, R204, R206, R208, R301, R302, R304, R306, R308, R401, R402, R404, R406, R408: 100k; R_0603_1608Metric; MPN 0603WAF1003T5E; LCSC C25803
R203, R205, R207, R303, R305, R307, R403, R405, R407: 100; R_0603_1608Metric; MPN 0603WAF1000T5E; LCSC C22775
RV201, RV202, RV203, RV301, RV302, RV303, RV401, RV402, RV403: 50k; Potentiometer_RV09
U201, U301, U401: TL072CDT; SOIC-8_3.9x4.9mm_P1.27mm; MPN TL072CDT; LCSC C6961

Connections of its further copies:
+12V: C202.1, C302.1, C402.1, U201.8 (V+), U301.8 (V+), U401.8 (V+); also elsewhere on the board
-12V: C203.2, C303.2, C403.2, U201.4 (V-), U301.4 (V-), U401.4 (V-); also elsewhere on the board
/CH2/BUF: C201.2, R202.2, R203.1, U201.1
/CH2/IN: C204.1, J201.T
/CH2/POST: R205.1, R207.1, U201.6 (-), U201.7
/CH2/VOL_W: R204.1, RV201.2, U201.5 (+)
/CH3/BUF: C301.2, R302.2, R303.1, U301.1
/CH3/IN: C304.1, J301.T
/CH3/POST: R305.1, R307.1, U301.6 (-), U301.7
/CH3/VOL_W: R304.1, RV301.2, U301.5 (+)
/CH4/BUF: C401.2, R402.2, R403.1, U401.1
/CH4/IN: C404.1, J401.T
/CH4/POST: R405.1, R407.1, U401.6 (-), U401.7
/CH4/VOL_W: R404.1, RV401.2, U401.5 (+)
/MAIN_SUM: R204.2, R304.2, R404.2; also elsewhere on the board
/SENDA_SUM: R206.2, R306.2, R406.2; also elsewhere on the board
/SENDB_SUM: R208.2, R308.2, R408.2; also elsewhere on the board
GND: C202.2, C203.1, C302.2, C303.1, C402.2, C403.1, J201.S, J201.TN, J301.S, J301.TN, J401.S, J401.TN, RV201.1, RV202.1, RV203.1, RV301.1, RV302.1, RV303.1, RV401.1, RV402.1, RV403.1, U201.3 (+), U301.3 (+), U401.3 (+); also elsewhere on the board
unnamed: C204.2, R201.1
unnamed: C304.2, R301.1
unnamed: C404.2, R401.1
unnamed: R203.2, RV201.3
unnamed: R205.2, RV202.3
unnamed: R206.1, RV202.2
unnamed: R207.2, RV203.3
unnamed: R208.1, RV203.2
unnamed: R303.2, RV301.3
unnamed: R305.2, RV302.3
unnamed: R306.1, RV302.2
unnamed: R307.2, RV303.3
unnamed: R308.1, RV303.2
unnamed: R403.2, RV401.3
unnamed: R405.2, RV402.3
unnamed: R406.1, RV402.2
unnamed: R407.2, RV403.3
unnamed: R408.1, RV403.2
unnamed: C201.1, R201.2, R202.1, U201.2 (-)
unnamed: C301.1, R301.2, R302.1, U301.2 (-)
unnamed: C401.1, R401.2, R402.1, U401.2 (-)

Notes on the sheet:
Bread Modular 4mix channel on +/-12 V: jack -> 10u -> 100k -> inverting buffer (100k || 20p, gain -1) -> 100R -> VOL (CW = pin 3). VOL wiper -> 100k -> MAIN_SUM. A unity follower buffers the wiper (post-fader) and drives SEND A / SEND B through 100R; each send wiper -> 100k -> SENDA_SUM / SENDB_SUM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
Taper: each wiper sees 100k to a virtual ground (as Bread Modular 4mix/imix), so the 50k B pots run slightly below linear (about 44 % at mid rotation).
CHANNEL STRIP (one sheet, used 4 times: CH1..CH4; parts n01.. per channel)
